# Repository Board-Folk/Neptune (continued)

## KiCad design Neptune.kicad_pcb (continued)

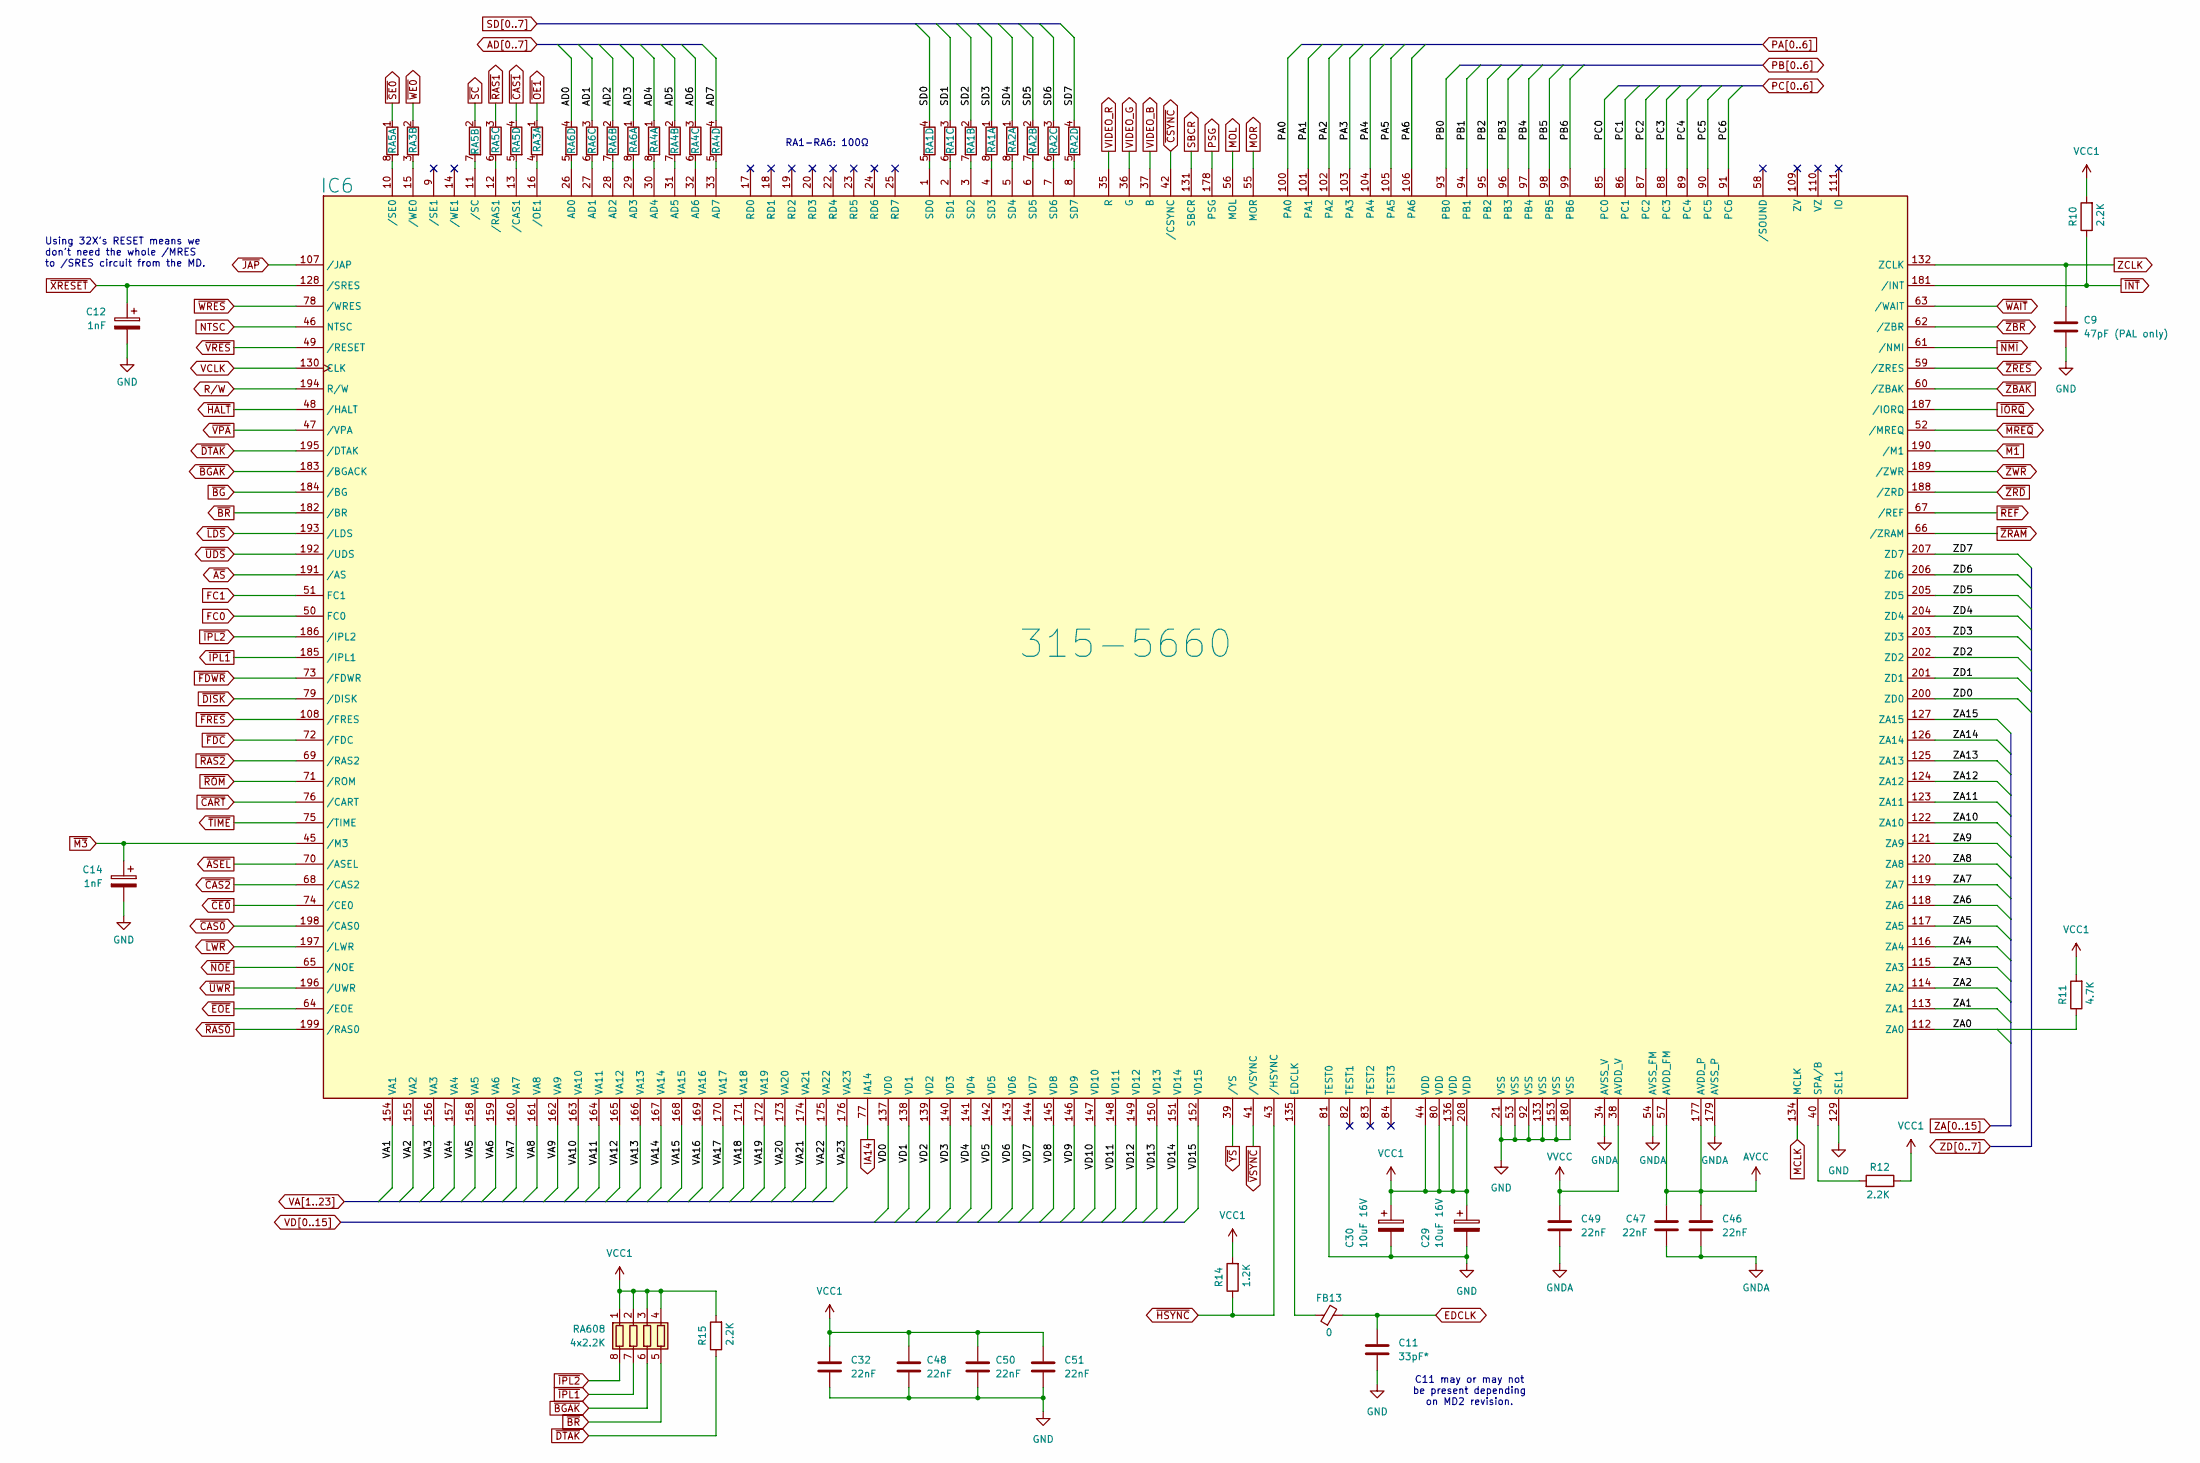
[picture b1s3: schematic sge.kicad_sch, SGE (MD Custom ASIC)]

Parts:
C9: 47pF (PAL only); C_0805_2012Metric; MPN VJ0805A470FXJPW1BC; LCSC Part # C149613
C11: 33pF*; C_0805_2012Metric; MPN VJ0805A330FXJPW1BC; LCSC Part # C520060
C12, C14: 1nF; C_0805_2012Metric; MPN VJ0805Y105KXJTW1BC; LCSC Part # C541528
C29, C30: 10uF 16V; CP_Radial_D5.0mm_P2.50mm
C32, C46, C47, C48, C49, C50, C51: 22nF; C_0805_2012Metric; MPN VJ0805Y223JXJPW1BC; LCSC Part # C520037
FB13: 0; L_0805_2012Metric; MPN CBG201209U000T; LCSC Part # C91037
IC6: 315-5660; QFP-208_28x28_Pitch0.5mm
R10, R12, R15: 2.2K; R_0805_2012Metric; MPN CRCW08052K20JNEA; DigiKey P2.20KCCT-ND
R11: 4.7K; R_0805_2012Metric; MPN CRCW08054K70JNEAC; LCSC Part # C2077067
R14: 1.2K; R_0805_2012Metric; MPN CRCW08051K20FKEAHP; LCSC Part # C136926
RA1, RA2, RA4, RA5, RA6: 4x100; R_Array_Convex_4x0603; MPN YC164-FR-07100RL; LCSC Part # C1852225
RA3: 2x100; R_Array_Convex_2x0603; MPN YC162-FR-07100RL; LCSC Part # C728824
RA608: 4x2.2K; R_Array_Convex_4x0603; MPN YC164-JR-072K2L; LCSC Part # C136829

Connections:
AD0: RA6.4 (R4.1); also elsewhere on the board
AD1: RA6.3 (R3.1); also elsewhere on the board
AD2: RA6.2 (R2.1); also elsewhere on the board
AD3: RA6.1 (R1.1); also elsewhere on the board
AD4: RA4.1 (R1.1); also elsewhere on the board
AD5: RA4.2 (R2.1); also elsewhere on the board
AD6: RA4.3 (R3.1); also elsewhere on the board
AD7: RA4.4 (R4.1); also elsewhere on the board
AVCC: C29.1, C30.1, C32.1, C46.1, C47.1, C48.1, C49.1, C50.1, C51.1, IC6.38 (AVDD_V), IC6.44 (VDD), IC6.57 (AVDD_FM), IC6.80 (VDD), IC6.136 (VDD), IC6.177 (AVDD_P), IC6.208 (VDD), R10.2, R11.2, R12.1, R14.2, R15.2, RA608.1 (R1.1), RA608.2 (R2.1), RA608.3 (R3.1), RA608.4 (R4.1); also elsewhere on the board
EDCLK: C11.1, FB13.2; also elsewhere on the board
FC0: IC6.50 (FC0); also elsewhere on the board
FC1: IC6.51 (FC1); also elsewhere on the board
GND: C9.2, C11.2, C12.2, C14.2, C29.2, C30.2, C32.2, C46.2, C47.2, C48.2, C49.2, C50.2, C51.2, IC6.21 (VSS), IC6.34 (AVSS_V), IC6.53 (VSS), IC6.54 (AVSS_FM), IC6.81 (TEST0), IC6.92 (VSS), IC6.129 (SEL1), IC6.133 (VSS), IC6.153 (VSS), IC6.179 (AVSS_P), IC6.180 (VSS); also elsewhere on the board
IA14: IC6.77 (IA14); also elsewhere on the board
MCLK: IC6.134 (MCLK); also elsewhere on the board
MOL: IC6.56 (MOL); also elsewhere on the board
MOR: IC6.55 (MOR); also elsewhere on the board
NTSC: IC6.46 (NTSC); also elsewhere on the board
unnamed: IC6.26 (AD0), RA6.5 (R4.2)
unnamed: IC6.27 (AD1), RA6.6 (R3.2)
unnamed: IC6.28 (AD2), RA6.7 (R2.2)
unnamed: IC6.29 (AD3), RA6.8 (R1.2)
unnamed: IC6.30 (AD4), RA4.8 (R1.2)
unnamed: IC6.31 (AD5), RA4.7 (R2.2)
unnamed: IC6.32 (AD6), RA4.6 (R3.2)
unnamed: IC6.33 (AD7), RA4.5 (R4.2)
unnamed: FB13.1, IC6.135 (EDCLK)
unnamed: IC6.1 (SD0), RA1.5 (R4.2)
unnamed: IC6.2 (SD1), RA1.6 (R3.2)
unnamed: IC6.3 (SD2), RA1.7 (R2.2)
unnamed: IC6.4 (SD3), RA1.8 (R1.2)
unnamed: IC6.5 (SD4), RA2.8 (R1.2)
unnamed: IC6.6 (SD5), RA2.7 (R2.2)
unnamed: IC6.7 (SD6), RA2.6 (R3.2)
unnamed: IC6.8 (SD7), RA2.5 (R4.2)
unnamed: IC6.40 (SPA/B), R12.2
unnamed: IC6.13 (/CAS1), RA5.5 (R4.2)
unnamed: IC6.16 (/OE1), RA3.4 (R1.2)
unnamed: IC6.12 (/RAS1), RA5.6 (R3.2)
unnamed: IC6.11 (/SC), RA5.7 (R2.2)
unnamed: IC6.10 (/SE0), RA5.8 (R1.2)
unnamed: IC6.15 (/WE0), RA3.3 (R2.2)
PA0: IC6.100 (PA0); also elsewhere on the board
PA1: IC6.101 (PA1); also elsewhere on the board
PA2: IC6.102 (PA2); also elsewhere on the board
PA3: IC6.103 (PA3); also elsewhere on the board
PA4: IC6.104 (PA4); also elsewhere on the board
PA5: IC6.105 (PA5); also elsewhere on the board
PA6: IC6.106 (PA6); also elsewhere on the board
PB0: IC6.93 (PB0); also elsewhere on the board
PB1: IC6.94 (PB1); also elsewhere on the board
PB2: IC6.95 (PB2); also elsewhere on the board
PB3: IC6.96 (PB3); also elsewhere on the board
PB4: IC6.97 (PB4); also elsewhere on the board
PB5: IC6.98 (PB5); also elsewhere on the board
PB6: IC6.99 (PB6); also elsewhere on the board
PC0: IC6.85 (PC0); also elsewhere on the board
PC1: IC6.86 (PC1); also elsewhere on the board
PC2: IC6.87 (PC2); also elsewhere on the board
PC3: IC6.88 (PC3); also elsewhere on the board
PC4: IC6.89 (PC4); also elsewhere on the board
PC5: IC6.90 (PC5); also elsewhere on the board
PC6: IC6.91 (PC6); also elsewhere on the board
PSG: IC6.178 (PSG); also elsewhere on the board
R/W: IC6.194 (R/W); also elsewhere on the board
SBCR: IC6.131 (SBCR); also elsewhere on the board
SD0: RA1.4 (R4.1); also elsewhere on the board
SD1: RA1.3 (R3.1); also elsewhere on the board
SD2: RA1.2 (R2.1); also elsewhere on the board
SD3: RA1.1 (R1.1); also elsewhere on the board
SD4: RA2.1 (R1.1); also elsewhere on the board
SD5: RA2.2 (R2.1); also elsewhere on the board
SD6: RA2.3 (R3.1); also elsewhere on the board
SD7: RA2.4 (R4.1); also elsewhere on the board
VA1: IC6.154 (VA1); also elsewhere on the board
VA2: IC6.155 (VA2); also elsewhere on the board
VA3: IC6.156 (VA3); also elsewhere on the board
VA4: IC6.157 (VA4); also elsewhere on the board
VA5: IC6.158 (VA5); also elsewhere on the board
VA6: IC6.159 (VA6); also elsewhere on the board
VA7: IC6.160 (VA7); also elsewhere on the board
VA8: IC6.161 (VA8); also elsewhere on the board
VA9: IC6.162 (VA9); also elsewhere on the board
VA10: IC6.163 (VA10); also elsewhere on the board
VA11: IC6.164 (VA11); also elsewhere on the board
VA12: IC6.165 (VA12); also elsewhere on the board
VA13: IC6.166 (VA13); also elsewhere on the board
VA14: IC6.167 (VA14); also elsewhere on the board
VA15: IC6.168 (VA15); also elsewhere on the board
VA16: IC6.169 (VA16); also elsewhere on the board
VA17: IC6.170 (VA17); also elsewhere on the board
VA18: IC6.171 (VA18); also elsewhere on the board
VA19: IC6.172 (VA19); also elsewhere on the board
VA20: IC6.173 (VA20); also elsewhere on the board
VA21: IC6.174 (VA21); also elsewhere on the board
VA22: IC6.175 (VA22); also elsewhere on the board
VA23: IC6.176 (VA23); also elsewhere on the board
VCLK: IC6.130 (CLK); also elsewhere on the board
VD0: IC6.137 (VD0); also elsewhere on the board
VD1: IC6.138 (VD1); also elsewhere on the board
VD2: IC6.139 (VD2); also elsewhere on the board
VD3: IC6.140 (VD3); also elsewhere on the board
VD4: IC6.141 (VD4); also elsewhere on the board
VD5: IC6.142 (VD5); also elsewhere on the board
VD6: IC6.143 (VD6); also elsewhere on the board
VD7: IC6.144 (VD7); also elsewhere on the board
VD8: IC6.145 (VD8); also elsewhere on the board
VD9: IC6.146 (VD9); also elsewhere on the board
VD10: IC6.147 (VD10); also elsewhere on the board
VD11: IC6.148 (VD11); also elsewhere on the board
VD12: IC6.149 (VD12); also elsewhere on the board
VD13: IC6.150 (VD13); also elsewhere on the board
VD14: IC6.151 (VD14); also elsewhere on the board
VD15: IC6.152 (VD15); also elsewhere on the board
VIDEO_B: IC6.37 (B); also elsewhere on the board
VIDEO_G: IC6.36 (G); also elsewhere on the board
VIDEO_R: IC6.35 (R); also elsewhere on the board
ZA0: IC6.112 (ZA0), R11.1; also elsewhere on the board
ZA1: IC6.113 (ZA1); also elsewhere on the board
ZA2: IC6.114 (ZA2); also elsewhere on the board
ZA3: IC6.115 (ZA3); also elsewhere on the board
ZA4: IC6.116 (ZA4); also elsewhere on the board
ZA5: IC6.117 (ZA5); also elsewhere on the board
ZA6: IC6.118 (ZA6); also elsewhere on the board
ZA7: IC6.119 (ZA7); also elsewhere on the board
ZA8: IC6.120 (ZA8); also elsewhere on the board
ZA9: IC6.121 (ZA9); also elsewhere on the board
ZA10: IC6.122 (ZA10); also elsewhere on the board
ZA11: IC6.123 (ZA11); also elsewhere on the board
ZA12: IC6.124 (ZA12); also elsewhere on the board
ZA13: IC6.125 (ZA13); also elsewhere on the board
ZA14: IC6.126 (ZA14); also elsewhere on the board
ZA15: IC6.127 (ZA15); also elsewhere on the board
ZCLK: C9.1, IC6.132 (ZCLK); also elsewhere on the board
ZD0: IC6.200 (ZD0); also elsewhere on the board
ZD1: IC6.201 (ZD1); also elsewhere on the board
ZD2: IC6.202 (ZD2); also elsewhere on the board
ZD3: IC6.203 (ZD3); also elsewhere on the board
ZD4: IC6.204 (ZD4); also elsewhere on the board
ZD5: IC6.205 (ZD5); also elsewhere on the board
ZD6: IC6.206 (ZD6); also elsewhere on the board
ZD7: IC6.207 (ZD7); also elsewhere on the board
~ASEL: IC6.70 (/ASEL); also elsewhere on the board
~AS: IC6.191 (/AS); also elsewhere on the board
~BGAK: IC6.183 (/BGACK), RA608.6 (R3.2); also elsewhere on the board
~BG: IC6.184 (/BG); also elsewhere on the board
~BR: IC6.182 (/BR), RA608.5 (R4.2); also elsewhere on the board
~CART: IC6.76 (/CART); also elsewhere on the board
~CAS0: IC6.198 (/CAS0); also elsewhere on the board
~CAS1: RA5.4 (R4.1); also elsewhere on the board
~CAS2: IC6.68 (/CAS2); also elsewhere on the board
~CE0: IC6.74 (/CE0); also elsewhere on the board
~CSYNC: IC6.42 (/CSYNC); also elsewhere on the board
~DISK: IC6.79 (/DISK); also elsewhere on the board
~DTAK: IC6.195 (/DTAK), R15.1; also elsewhere on the board
~EOE: IC6.64 (/EOE); also elsewhere on the board
~FDC: IC6.72 (/FDC); also elsewhere on the board
~FDWR: IC6.73 (/FDWR); also elsewhere on the board
~FRES: IC6.108 (/FRES); also elsewhere on the board
~HALT: IC6.48 (/HALT); also elsewhere on the board
~HSYNC: IC6.43 (/HSYNC), R14.1; also elsewhere on the board
~INT: IC6.181 (/INT), R10.1; also elsewhere on the board
~IORQ: IC6.187 (/IORQ); also elsewhere on the board
~IPL1: IC6.185 (/IPL1), RA608.7 (R2.2); also elsewhere on the board
~IPL2: IC6.186 (/IPL2), RA608.8 (R1.2); also elsewhere on the board
~JAP: IC6.107 (/JAP); also elsewhere on the board
~LDS: IC6.193 (/LDS); also elsewhere on the board
~LWR: IC6.197 (/LWR); also elsewhere on the board
~M1: IC6.190 (/M1); also elsewhere on the board
~M3: C14.1, IC6.45 (/M3); also elsewhere on the board
~MREQ: IC6.52 (/MREQ); also elsewhere on the board
~NMI: IC6.61 (/NMI); also elsewhere on the board
~NOE: IC6.65 (/NOE); also elsewhere on the board
~OE1: RA3.1 (R1.1); also elsewhere on the board
~RAS0: IC6.199 (/RAS0); also elsewhere on the board
~RAS1: RA5.3 (R3.1); also elsewhere on the board
~RAS2: IC6.69 (/RAS2); also elsewhere on the board
~REF: IC6.67 (/REF); also elsewhere on the board
~ROM: IC6.71 (/ROM); also elsewhere on the board
~SC: RA5.2 (R2.1); also elsewhere on the board
~SE0: RA5.1 (R1.1); also elsewhere on the board
~TIME: IC6.75 (/TIME); also elsewhere on the board
~UDS: IC6.192 (/UDS); also elsewhere on the board
~UWR: IC6.196 (/UWR); also elsewhere on the board
~VPA: IC6.47 (/VPA); also elsewhere on the board
~VRES: IC6.49 (/RESET); also elsewhere on the board
~VSYNC: IC6.41 (/VSYNC); also elsewhere on the board
~WAIT: IC6.63 (/WAIT); also elsewhere on the board
~WE0: RA3.2 (R2.1); also elsewhere on the board
~WRES: IC6.78 (/WRES); also elsewhere on the board
~XRESET: C12.1, IC6.128 (/SRES); also elsewhere on the board
~YS: IC6.39 (/YS); also elsewhere on the board
~ZBAK: IC6.60 (/ZBAK); also elsewhere on the board
~ZBR: IC6.62 (/ZBR); also elsewhere on the board
~ZRAM: IC6.66 (/ZRAM); also elsewhere on the board
~ZRD: IC6.188 (/ZRD); also elsewhere on the board
~ZRES: IC6.59 (/ZRES); also elsewhere on the board
~ZWR: IC6.189 (/ZWR); also elsewhere on the board

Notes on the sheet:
Using 32X's RESET means we don't need the whole /MRES to /SRES circuit from the MD.
RA1-RA6: 100Ω
C11 may or may not be present depending on MD2 revision.

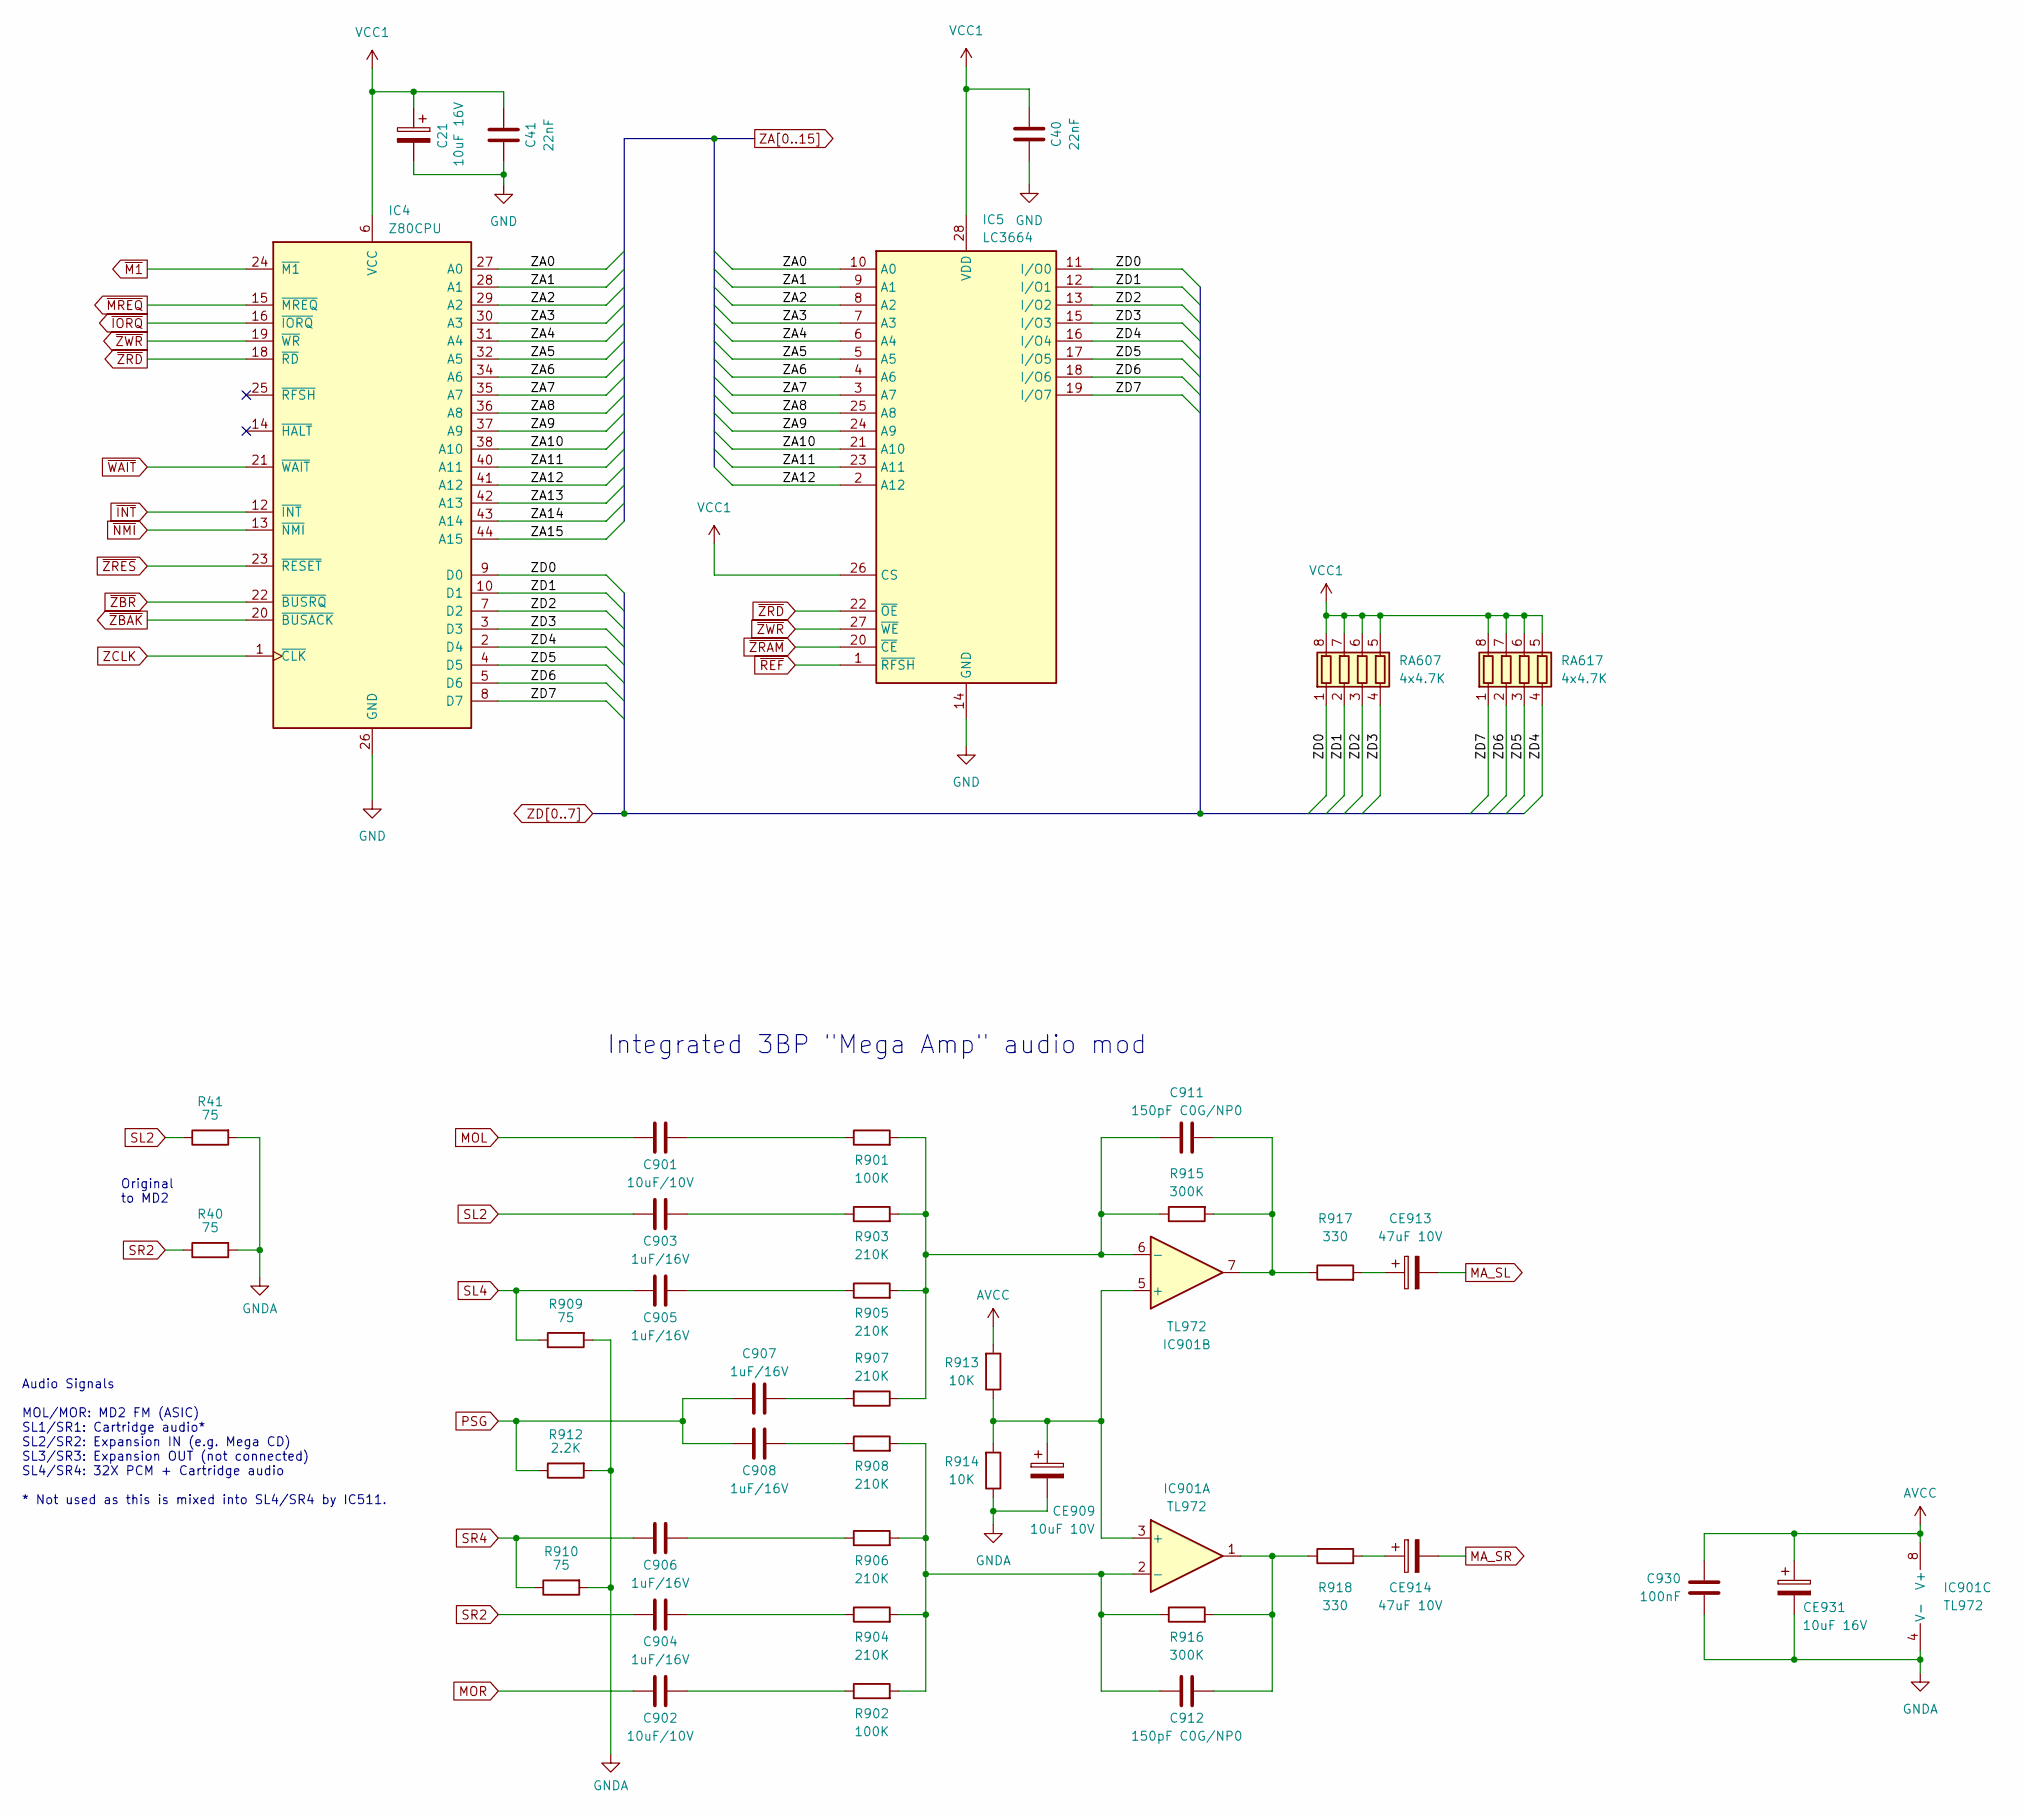
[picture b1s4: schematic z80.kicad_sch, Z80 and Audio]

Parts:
C21: 10uF 16V; CP_Radial_D5.0mm_P2.50mm
C40, C41: 22nF; C_0805_2012Metric; MPN VJ0805Y223JXJPW1BC; LCSC Part # C520037
C901, C902: 10uF/10V; C_0805_2012Metric; MPN VJ0805V106ZXQTW1BC; DigiKey 1276-1096-1-ND
C903, C904, C905, C906, C907, C908: 1uF/16V; C_0805_2012Metric; MPN VJ0805Y105KXJTW1BC; LCSC Part # C94122
C911, C912: 150pF C0G/NP0; C_0805_2012Metric; MPN VJ0805A151FXJCW1BC; DigiKey 311-4166-1-ND
C930: 100nF; C_0805_2012Metric; MPN VJ0805Y104JXJMT; LCSC Part # C111492
CE909: 10uF 10V; CP_Radial_D5.0mm_P2.50mm; DigiKey P15787CT-ND
CE913, CE914: 47uF 10V; CP_Radial_D5.0mm_P2.50mm; DigiKey 493-13447-1-ND
CE931: 10uF 16V; CP_Radial_D5.0mm_P2.50mm
IC4: Z80CPU; QFP-44_10x10_Pitch0.8mm
IC5: LC3664; SOIC-28W_7.5x18.7mm_P1.27mm
IC901: TL972; SO-8_3.9x4.9mm_P1.27mm; MPN TL972IDR; DigiKey 296-21693-1-ND
R40, R41, R909, R910: 75; R_0805_2012Metric; MPN CRCW080575R0FKEAHP; DigiKey P75.0CCT-ND
R901, R902: 100K; R_0805_2012Metric; MPN CRCW0805100KFKEA; LCSC Part # C844935
R903, R904, R905, R906, R907, R908: 210K; R_0805_2012Metric; MPN CRCW0805210KFKEA; DigiKey P210KCCT-ND
R912: 2.2K; R_0805_2012Metric; MPN CRCW08052K20JNEA; DigiKey P2.20KCCT-ND
R913, R914: 10K; R_0805_2012Metric; MPN CRCW080510K0FKEA; LCSC Part # C844937
R915, R916: 300K; R_0805_2012Metric; MPN RCS0805300KFKEA; DigiKey P300KCCT-ND
R917, R918: 330; R_0805_2012Metric; MPN CRCW0805330RFKEA; LCSC Part # C844839
RA607, RA617: 4x4.7K; R_Array_Convex_4x0603; MPN YC164-FR-074K7L; LCSC Part # C700514

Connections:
AVCC: C21.1, C40.2, C41.2, C930.1, CE931.1, IC4.6 (VCC), IC5.26 (CS), IC5.28 (VDD), IC901.8 (V+), R913.2, RA607.5 (R4.2), RA607.6 (R3.2), RA607.7 (R2.2), RA607.8 (R1.2), RA617.5 (R4.2), RA617.6 (R3.2), RA617.7 (R2.2), RA617.8 (R1.2); also elsewhere on the board
GND: C21.2, C40.1, C41.1, C930.2, CE909.2, CE931.2, IC4.26 (GND), IC5.14 (GND), IC901.4 (V-), R40.2, R41.2, R909.2, R910.2, R912.2, R914.1; also elsewhere on the board
MA_SL: CE913.2; also elsewhere on the board
MA_SR: CE914.2; also elsewhere on the board
MOL: C901.1; also elsewhere on the board
MOR: C902.1; also elsewhere on the board
unnamed: C901.2, R901.1
unnamed: C902.2, R902.1
unnamed: C903.2, R903.1
unnamed: C904.2, R904.1
unnamed: C905.2, R905.1
unnamed: C906.2, R906.1
unnamed: C907.2, R907.2
unnamed: C908.2, R908.1
unnamed: C911.2, IC901.7, R915.2, R917.1
unnamed: C912.2, IC901.1, R916.2, R918.1
unnamed: CE913.1, R917.2
unnamed: CE914.1, R918.2
unnamed: CE909.1, IC901.3 (+), IC901.5 (+), R913.1, R914.2
unnamed: C912.1, IC901.2 (-), R902.2, R904.2, R906.2, R908.2, R916.1
unnamed: C911.1, IC901.6 (-), R901.2, R903.2, R905.2, R907.1, R915.1
PSG: C907.1, C908.1, R912.1; also elsewhere on the board
SL2: C903.1, R41.1; also elsewhere on the board
SL4: C905.1, R909.1; also elsewhere on the board
SR2: C904.1, R40.1; also elsewhere on the board
SR4: C906.1, R910.1; also elsewhere on the board
ZA0: IC4.27 (A0), IC5.10 (A0); also elsewhere on the board
ZA1: IC4.28 (A1), IC5.9 (A1); also elsewhere on the board
ZA2: IC4.29 (A2), IC5.8 (A2); also elsewhere on the board
ZA3: IC4.30 (A3), IC5.7 (A3); also elsewhere on the board
ZA4: IC4.31 (A4), IC5.6 (A4); also elsewhere on the board
ZA5: IC4.32 (A5), IC5.5 (A5); also elsewhere on the board
ZA6: IC4.34 (A6), IC5.4 (A6); also elsewhere on the board
ZA7: IC4.35 (A7), IC5.3 (A7); also elsewhere on the board
ZA8: IC4.36 (A8), IC5.25 (A8); also elsewhere on the board
ZA9: IC4.37 (A9), IC5.24 (A9); also elsewhere on the board
ZA10: IC4.38 (A10), IC5.21 (A10); also elsewhere on the board
ZA11: IC4.40 (A11), IC5.23 (A11); also elsewhere on the board
ZA12: IC4.41 (A12), IC5.2 (A12); also elsewhere on the board
ZA13: IC4.42 (A13); also elsewhere on the board
ZA14: IC4.43 (A14); also elsewhere on the board
ZA15: IC4.44 (A15); also elsewhere on the board
ZCLK: IC4.1 (~CLK); also elsewhere on the board
ZD0: IC4.9 (D0), IC5.11 (I/O0), RA607.1 (R1.1); also elsewhere on the board
ZD1: IC4.10 (D1), IC5.12 (I/O1), RA607.2 (R2.1); also elsewhere on the board
ZD2: IC4.7 (D2), IC5.13 (I/O2), RA607.3 (R3.1); also elsewhere on the board
ZD3: IC4.3 (D3), IC5.15 (I/O3), RA607.4 (R4.1); also elsewhere on the board
ZD4: IC4.2 (D4), IC5.16 (I/O4), RA617.4 (R4.1); also elsewhere on the board
ZD5: IC4.4 (D5), IC5.17 (I/O5), RA617.3 (R3.1); also elsewhere on the board
ZD6: IC4.5 (D6), IC5.18 (I/O6), RA617.2 (R2.1); also elsewhere on the board
ZD7: IC4.8 (D7), IC5.19 (I/O7), RA617.1 (R1.1); also elsewhere on the board
~INT: IC4.12 (~INT); also elsewhere on the board
~IORQ: IC4.16 (~IORQ); also elsewhere on the board
~M1: IC4.24 (~M1); also elsewhere on the board
~MREQ: IC4.15 (~MREQ); also elsewhere on the board
~NMI: IC4.13 (~NMI); also elsewhere on the board
~REF: IC5.1 (~RFSH); also elsewhere on the board
~WAIT: IC4.21 (~WAIT); also elsewhere on the board
~ZBAK: IC4.20 (~BUSACK); also elsewhere on the board
~ZBR: IC4.22 (~BUSRQ); also elsewhere on the board
~ZRAM: IC5.20 (~CE); also elsewhere on the board
~ZRD: IC4.18 (~RD), IC5.22 (~OE); also elsewhere on the board
~ZRES: IC4.23 (~RESET); also elsewhere on the board
~ZWR: IC4.19 (~WR), IC5.27 (~WE); also elsewhere on the board

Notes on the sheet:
Original to MD2
Audio Signals MOL/MOR: MD2 FM (ASIC) SL1/SR1: Cartridge audio* SL2/SR2: Expansion IN (e.g. Mega CD) SL3/SR3: Expansion OUT (not connected) SL4/SR4: 32X PCM + Cartridge audio * Not used as this is mixed into SL4/SR4 by IC511.
Integrated 3BP "Mega Amp" audio mod
